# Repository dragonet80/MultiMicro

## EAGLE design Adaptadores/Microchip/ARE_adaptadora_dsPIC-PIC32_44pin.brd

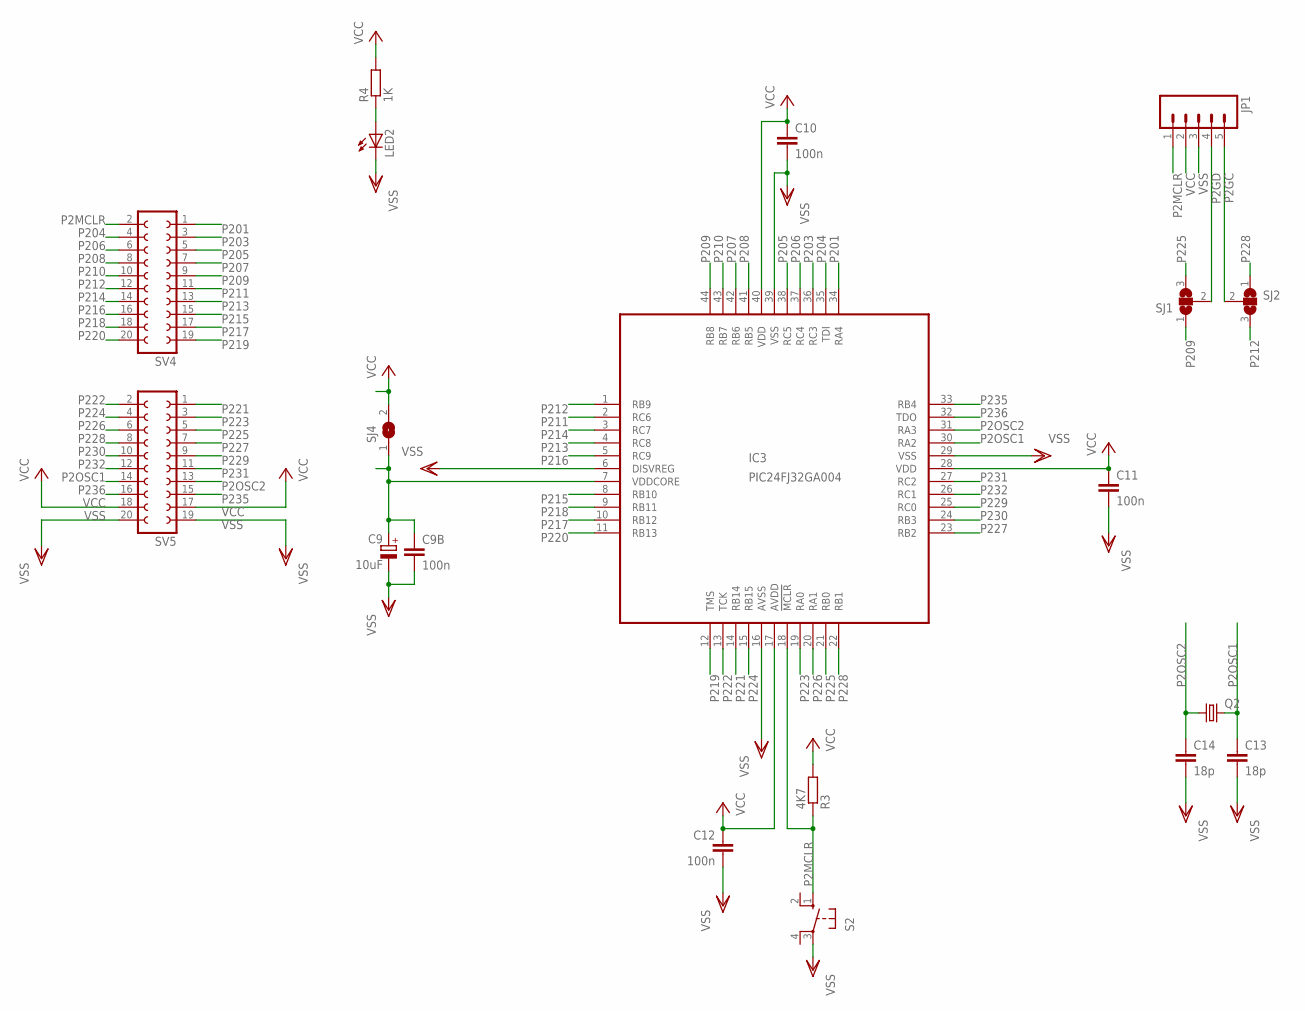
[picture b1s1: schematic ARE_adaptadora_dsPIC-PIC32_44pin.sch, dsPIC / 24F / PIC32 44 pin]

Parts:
C9: 10uF; SMC_C
C9B, C10, C11, C12: 100n; C0805
C13, C14: 18p; C0805
IC3: PIC24FJ32GA004; TQFP44
JP1: M05PTH; 1X05
LED2: LEDCHIPLED_0805; CHIPLED_0805
Q2: CRYSTALHC18U-V; HC18U-V
R3: 4K7; R0805
R4: 1K; R0805
S2: 10-XX; B3F-10XX; MPN B3F-1000
SJ1, SJ2: SJ2W; SJ_2
SJ4: SJ
SV4, SV5: FE10-2W

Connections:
unnamed: LED2.A, R4.1
unnamed: C9.+, C9B.1, IC3.7 (VDDCORE), SJ4.1
P2GC: JP1.5, SJ2.2
P2GD: JP1.4, SJ1.2
P2MCLR: IC3.18 (!MCLR), JP1.1, R3.1, S2.1 (S), SV4.2
P2OSC1: C13.1, IC3.30 (RA2), Q2.2, SV5.14
P2OSC2: C14.1, IC3.31 (RA3), Q2.1, SV5.13
P201: IC3.34 (RA4), SV4.1
P203: IC3.36 (RC3), SV4.3
P204: IC3.35 (TDI), SV4.4
P205: IC3.38 (RC5), SV4.5
P206: IC3.37 (RC4), SV4.6
P207: IC3.42 (RB6), SV4.7
P208: IC3.41 (RB5), SV4.8
P209: IC3.44 (RB8), SJ1.1, SV4.9
P210: IC3.43 (RB7), SV4.10
P211: IC3.2 (RC6), SV4.11
P212: IC3.1 (RB9), SJ2.3, SV4.12
P213: IC3.4 (RC8), SV4.13
P214: IC3.3 (RC7), SV4.14
P215: IC3.8 (RB10), SV4.15
P216: IC3.5 (RC9), SV4.16
P217: IC3.10 (RB12), SV4.17
P218: IC3.9 (RB11), SV4.18
P219: IC3.12 (TMS), SV4.19
P220: IC3.11 (RB13), SV4.20
P221: IC3.14 (RB14), SV5.1
P222: IC3.13 (TCK), SV5.2
P223: IC3.19 (RA0), SV5.3
P224: IC3.15 (RB15), SV5.4
P225: IC3.21 (RB0), SJ1.3, SV5.5
P226: IC3.20 (RA1), SV5.6
P227: IC3.23 (RB2), SV5.7
P228: IC3.22 (RB1), SJ2.1, SV5.8
P229: IC3.25 (RC0), SV5.9
P230: IC3.24 (RB3), SV5.10
P231: IC3.27 (RC2), SV5.11
P232: IC3.26 (RC1), SV5.12
P235: IC3.33 (RB4), SV5.15
P236: IC3.32 (TDO), SV5.16
VCC: C10.1, C11.1, C12.1, IC3.17 (AVDD), IC3.28 (VDD), IC3.40 (VDD), JP1.2, R3.2, R4.2, SJ4.2, SV5.17, SV5.18
VSS: C9.-, C9B.2, C10.2, C11.2, C12.2, C13.2, C14.2, IC3.6 (DISVREG), IC3.16 (AVSS), IC3.29 (VSS), IC3.39 (VSS), JP1.3, LED2.C, S2.3, SV5.19, SV5.20

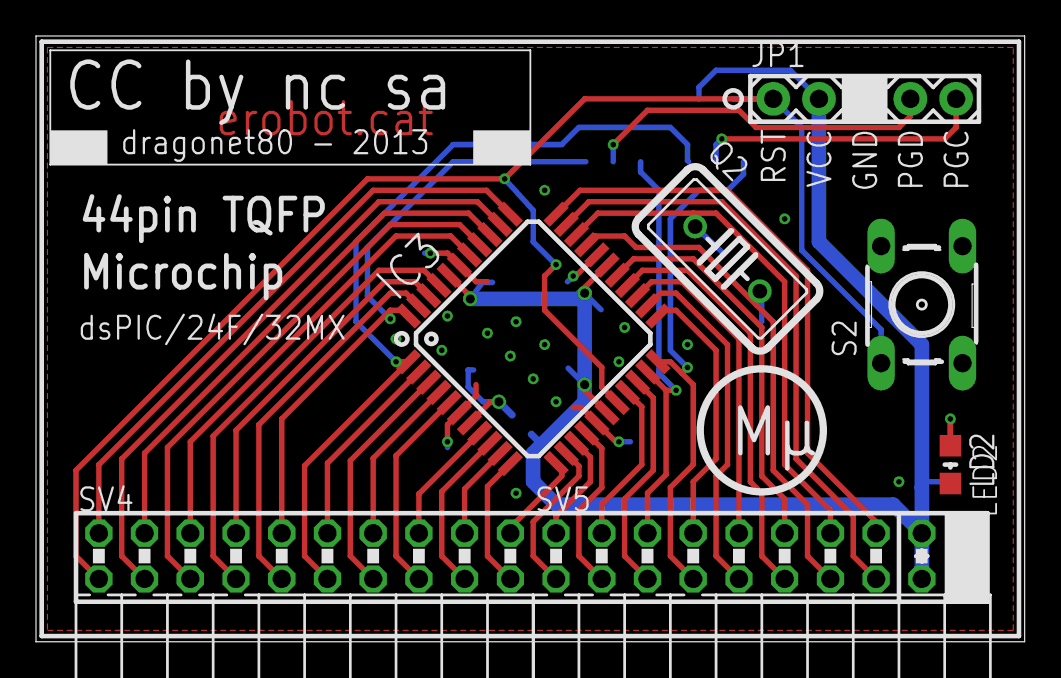
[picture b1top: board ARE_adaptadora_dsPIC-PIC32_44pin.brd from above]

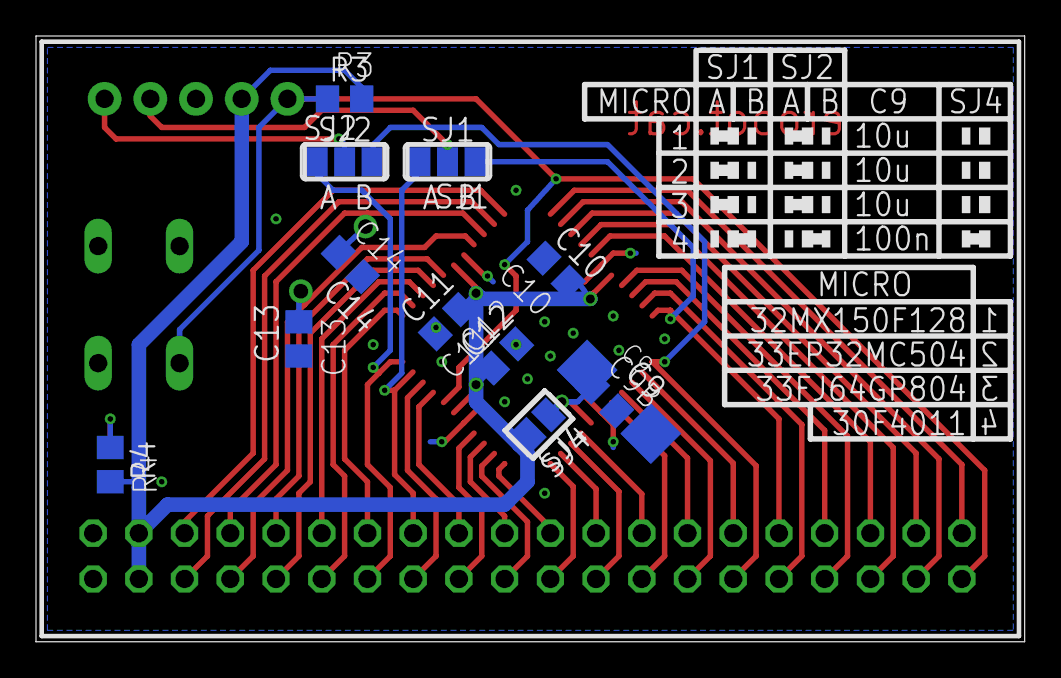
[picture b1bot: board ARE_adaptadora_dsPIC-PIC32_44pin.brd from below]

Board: 2 copper layers, 54.9 x 33.7 mm, 19 parts (12 on the bottom side), 42 nets.

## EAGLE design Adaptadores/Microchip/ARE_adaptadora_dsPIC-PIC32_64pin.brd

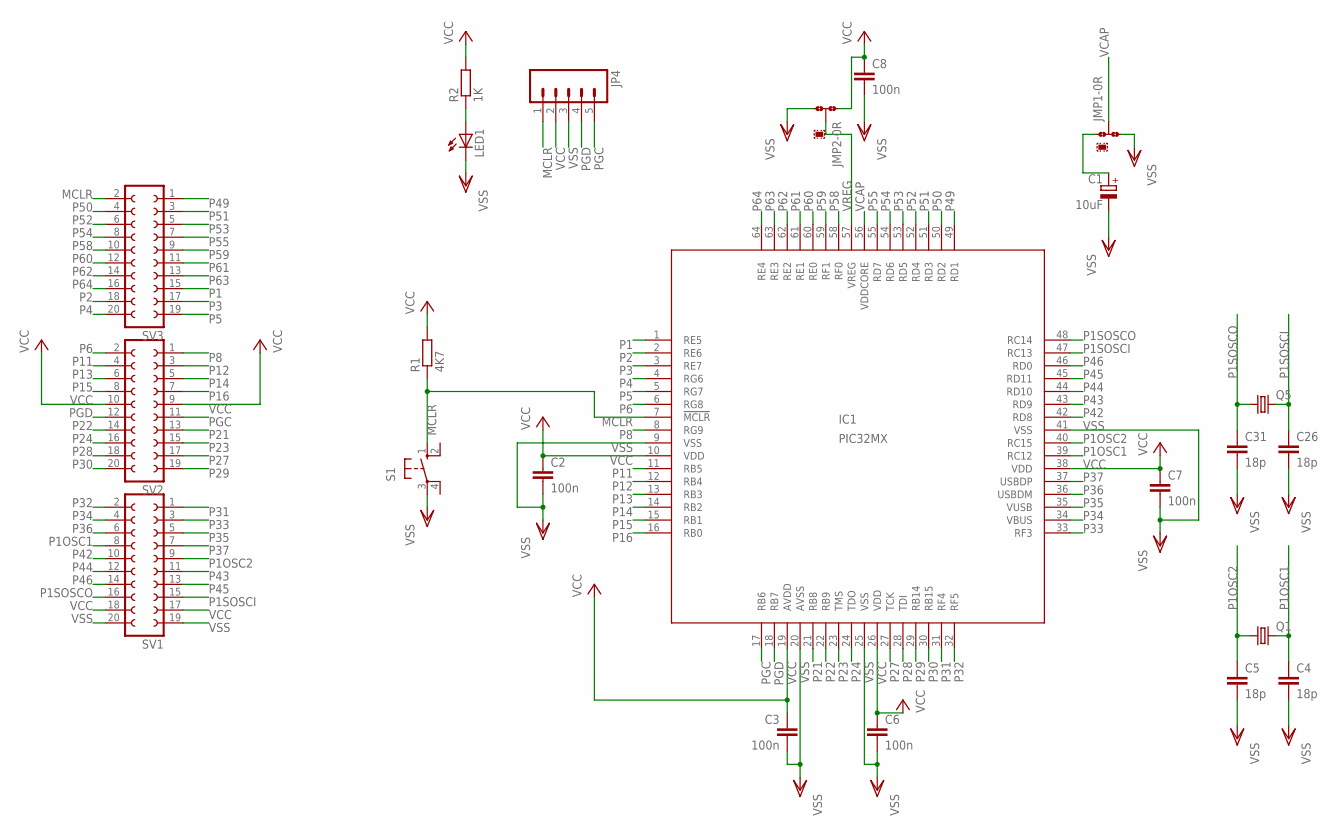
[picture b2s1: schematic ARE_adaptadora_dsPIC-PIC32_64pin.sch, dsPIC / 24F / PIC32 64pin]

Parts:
C1: 10uF; SMC_C
C2, C3, C6, C7, C8: 100n; C0805
C4, C5, C26, C31: 18p; C0805
IC1: PIC32MX; TQFP64-10X10
JMP1, JMP2: 0R-JUMPA; A0R-JMP
JP4: M05PTH; 1X05
LED1: LEDCHIPLED_0805; CHIPLED_0805
Q1, Q5: CRYSTALHC18U-V; HC18U-V
R1: 4K7; R0805
R2: 1K; R0805
S1: 10-XX; B3F-10XX; MPN B3F-1000
SV1, SV2, SV3: FE10-2W

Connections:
MCLR: IC1.7 (!MCLR), JP4.1, R1.1, S1.1 (S), SV3.2
unnamed: LED1.A, R2.1
unnamed: C1.+, JMP1.1
P1: IC1.1 (RE5), SV3.15
P1OSC1: C4.1, IC1.39 (RC12), Q1.2, SV1.8
P1OSC2: C5.1, IC1.40 (RC15), Q1.1, SV1.9
P1SOSCI: C26.1, IC1.47 (RC13), Q5.2, SV1.15
P1SOSCO: C31.1, IC1.48 (RC14), Q5.1, SV1.16
P2: IC1.2 (RE6), SV3.18
P3: IC1.3 (RE7), SV3.17
P4: IC1.4 (RG6), SV3.20
P5: IC1.5 (RG7), SV3.19
P6: IC1.6 (RG8), SV2.2
P8: IC1.8 (RG9), SV2.1
P11: IC1.11 (RB5), SV2.4
P12: IC1.12 (RB4), SV2.3
P13: IC1.13 (RB3), SV2.6
P14: IC1.14 (RB2), SV2.5
P15: IC1.15 (RB1), SV2.8
P16: IC1.16 (RB0), SV2.7
P21: IC1.21 (RB8), SV2.13
P22: IC1.22 (RB9), SV2.14
P23: IC1.23 (TMS), SV2.15
P24: IC1.24 (TDO), SV2.16
P27: IC1.27 (TCK), SV2.17
P28: IC1.28 (TDI), SV2.18
P29: IC1.29 (RB14), SV2.19
P30: IC1.30 (RB15), SV2.20
P31: IC1.31 (RF4), SV1.1
P32: IC1.32 (RF5), SV1.2
P33: IC1.33 (RF3), SV1.3
P34: IC1.34 (VBUS), SV1.4
P35: IC1.35 (VUSB), SV1.5
P36: IC1.36 (USBDM), SV1.6
P37: IC1.37 (USBDP), SV1.7
P42: IC1.42 (RD8), SV1.10
P43: IC1.43 (RD9), SV1.11
P44: IC1.44 (RD10), SV1.12
P45: IC1.45 (RD11), SV1.13
P46: IC1.46 (RD0), SV1.14
P49: IC1.49 (RD1), SV3.1
P50: IC1.50 (RD2), SV3.4
P51: IC1.51 (RD3), SV3.3
P52: IC1.52 (RD4), SV3.6
P53: IC1.53 (RD5), SV3.5
P54: IC1.54 (RD6), SV3.8
P55: IC1.55 (RD7), SV3.7
P58: IC1.58 (RF0), SV3.10
P59: IC1.59 (RF1), SV3.9
P60: IC1.60 (RE0), SV3.12
P61: IC1.61 (RE1), SV3.11
P62: IC1.62 (RE2), SV3.14
P63: IC1.63 (RE3), SV3.13
P64: IC1.64 (RE4), SV3.16
PGC: IC1.17 (RB6), JP4.5, SV2.11
PGD: IC1.18 (RB7), JP4.4, SV2.12
VCAP: IC1.56 (VDDCORE), JMP1.2
VCC: C2.1, C3.1, C6.1, C7.1, C8.1, IC1.10 (VDD), IC1.19 (AVDD), IC1.26 (VDD), IC1.38 (VDD), JMP2.1, JP4.2, R1.2, R2.2, SV1.17, SV1.18, SV2.9, SV2.10
VREG: IC1.57 (VREG), JMP2.2
VSS: C1.-, C2.2, C3.2, C4.2, C5.2, C6.2, C7.2, C8.2, C26.2, C31.2, IC1.9 (VSS), IC1.20 (AVSS), IC1.25 (VSS), IC1.41 (VSS), JMP1.3, JMP2.3, JP4.3, LED1.C, S1.3, SV1.19, SV1.20

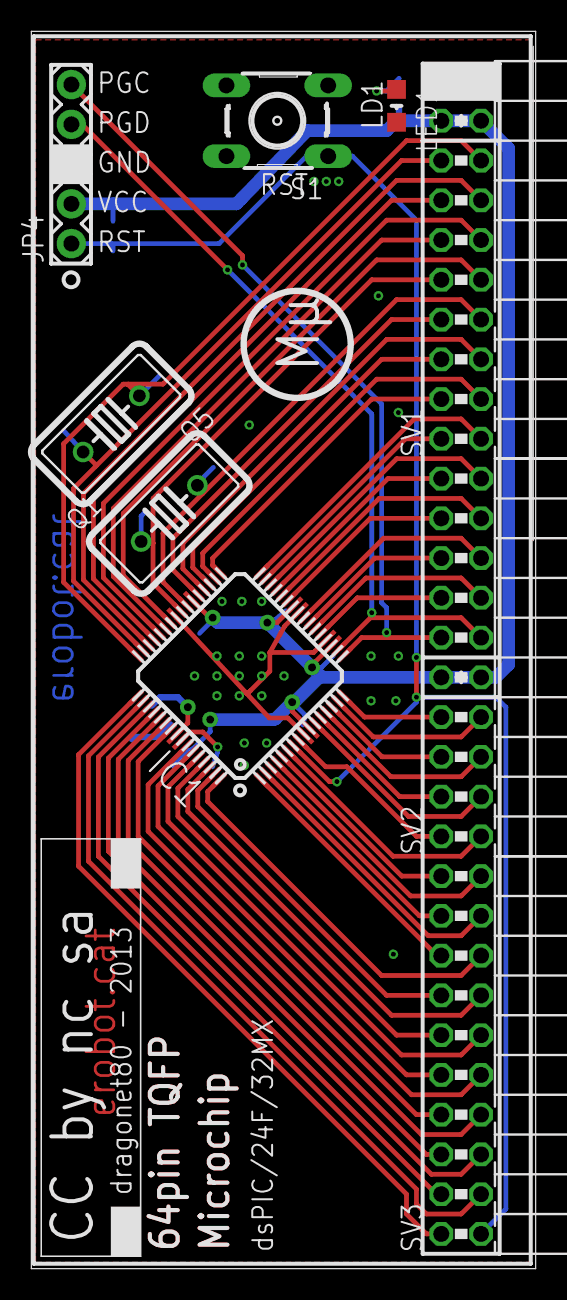
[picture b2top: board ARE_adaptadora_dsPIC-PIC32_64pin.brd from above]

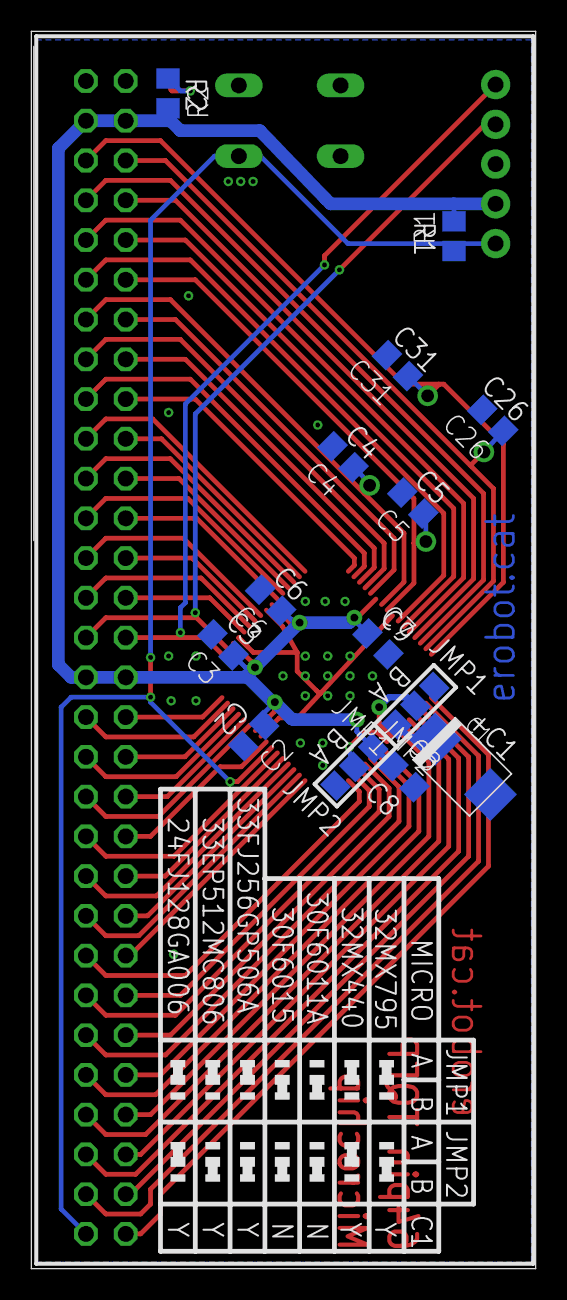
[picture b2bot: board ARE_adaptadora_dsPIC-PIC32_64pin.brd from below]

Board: 2 copper layers, 32.2 x 79.1 mm, 23 parts (14 on the bottom side), 60 nets.

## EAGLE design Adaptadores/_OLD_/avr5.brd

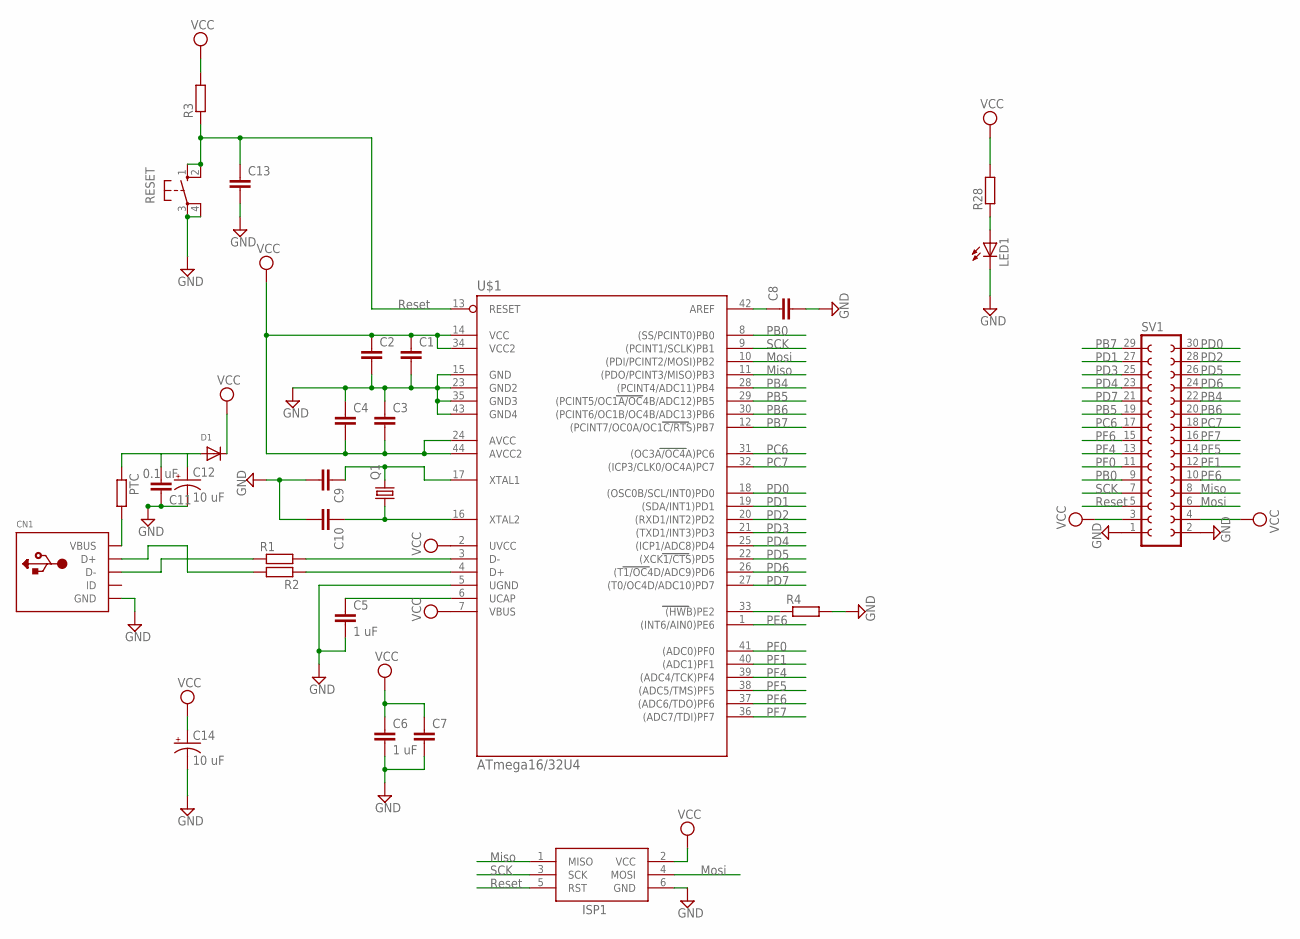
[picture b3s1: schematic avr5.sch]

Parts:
C1, C2, C3, C4, C7, C8, C9, C10, C13: C-EUC1206; C1206
C5, C6: 1 uF; C1206
C11: 0.1 uF; C1206
C12, C14: 10 uF; EIA3216
CN1: USBMINIB; USB-MINIB
D1: DIODESOD-123; SOD-123
ISP1: AVRISP-6; AVRISP
LED1: LEDCHIPLED_1206; CHIPLED_1206
PTC: R-EU_R1206; R1206
Q1: CRYSTALHC49UP; HC49UP
R1, R2, R3, R4, R28: R-EU_R1206; R1206
RESET: 10-XX; B3F-10XX
SV1: FE15-2
U$1: ATmega16/32U4; TQFP44

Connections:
GND: C1.2, C2.2, C3.1, C4.1, C5.2, C6.2, C7.2, C8.2, C9.2, C10.2, C11.2, C12.C (-), C13.2, C14.C (-), CN1.GND, ISP1.6 (GND), LED1.C, R4.2, RESET.3, RESET.4 (P1), SV1.1, SV1.2, U$1.5 (UGND), U$1.15 (GND), U$1.23 (GND2), U$1.35 (GND3), U$1.43 (GND4)
MISO: ISP1.1 (MISO), SV1.8, U$1.11 ((PDO/PCINT3/MISO)PB3)
MOSI: ISP1.4 (MOSI), SV1.6, U$1.10 ((PDI/PCINT2/MOSI)PB2)
unnamed: C9.1, Q1.2, U$1.17 (XTAL1)
unnamed: C10.1, Q1.1, U$1.16 (XTAL2)
unnamed: C5.1, U$1.6 (UCAP)
unnamed: R4.1, U$1.33 ((HWB)PE2)
unnamed: R2.1, U$1.4 (D+)
unnamed: R1.2, U$1.3 (D-)
unnamed: CN1.D+, R2.2
unnamed: CN1.D-, R1.1
unnamed: CN1.VBUS, PTC.2
unnamed: C11.1, C12.A (+), D1.A, PTC.1
unnamed: C8.1, U$1.42 (AREF)
unnamed: LED1.A, R28.1
PB0: SV1.9, U$1.8 ((SS/PCINT0)PB0)
PB4: SV1.22, U$1.28 ((PCINT4/ADC11)PB4)
PB5: SV1.19, U$1.29 ((PCINT5/OC1A/OC4B/ADC12)PB5)
PB6: SV1.20, U$1.30 ((PCINT6/OC1B/OC4B/ADC13)PB6)
PB7: SV1.29, U$1.12 ((PCINT7/OC0A/OC1C/RTS)PB7)
PC6: SV1.17, U$1.31 ((OC3A/OC4A)PC6)
PC7: SV1.18, U$1.32 ((ICP3/CLK0/OC4A)PC7)
PD0: SV1.30, U$1.18 ((OSC0B/SCL/INT0)PD0)
PD1: SV1.27, U$1.19 ((SDA/INT1)PD1)
PD2: SV1.28, U$1.20 ((RXD1/INT2)PD2)
PD3: SV1.25, U$1.21 ((TXD1/INT3)PD3)
PD4: SV1.23, U$1.25 ((ICP1/ADC8)PD4)
PD5: SV1.26, U$1.22 ((XCK1/CTS)PD5)
PD6: SV1.24, U$1.26 ((T1/OC4D/ADC9)PD6)
PD7: SV1.21, U$1.27 ((T0/OC4D/ADC10)PD7)
PE6: SV1.10, U$1.1 ((INT6/AIN0)PE6)
PF0: SV1.11, U$1.41 ((ADC0)PF0)
PF1: SV1.12, U$1.40 ((ADC1)PF1)
PF4: SV1.13, U$1.39 ((ADC4/TCK)PF4)
PF5: SV1.14, U$1.38 ((ADC5/TMS)PF5)
PF6: SV1.15, U$1.37 ((ADC6/TDO)PF6)
PF7: SV1.16, U$1.36 ((ADC7/TDI)PF7)
RESET: C13.1, ISP1.5 (RST), R3.1, RESET.1 (S), RESET.2 (S1), SV1.5, U$1.13 (RESET)
SCK: ISP1.3 (SCK), SV1.7, U$1.9 ((PCINT1/SCLK)PB1)
VCC: C1.1, C2.1, C3.2, C4.2, C6.1, C7.1, C14.A (+), D1.C, ISP1.2 (VCC), R3.2, R28.2, SV1.3, SV1.4, U$1.2 (UVCC), U$1.7 (VBUS), U$1.14 (VCC), U$1.24 (AVCC), U$1.34 (VCC2), U$1.44 (AVCC2)

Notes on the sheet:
Reset
Miso
Mosi
SCK
PB7
PB6
PB5
PB4
PB0
PC6
PC7
PD0
PD1
PD2
PD3
PD4
PD5
PD6
PD7
PE6
PF0
PF1
PF4
PF5
PF6
PF7

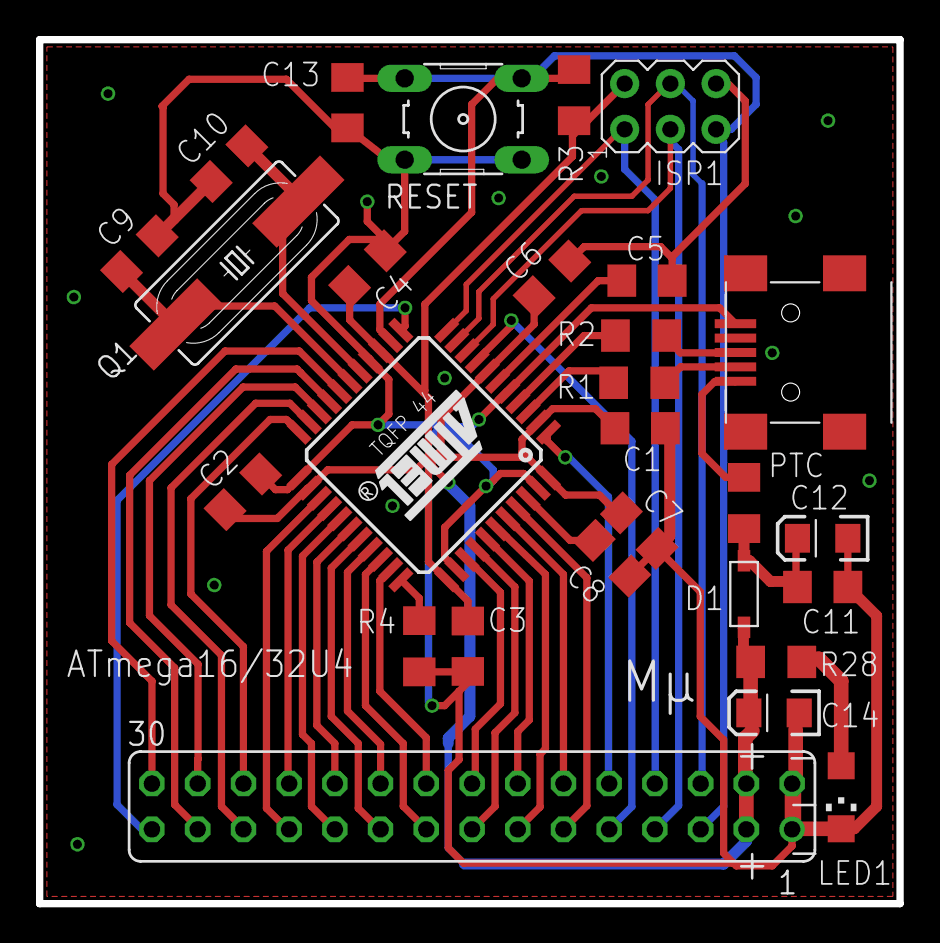
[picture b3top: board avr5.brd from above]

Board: 2 copper layers, 47.8 x 48.0 mm, 28 parts (0 on the bottom side), 40 nets.

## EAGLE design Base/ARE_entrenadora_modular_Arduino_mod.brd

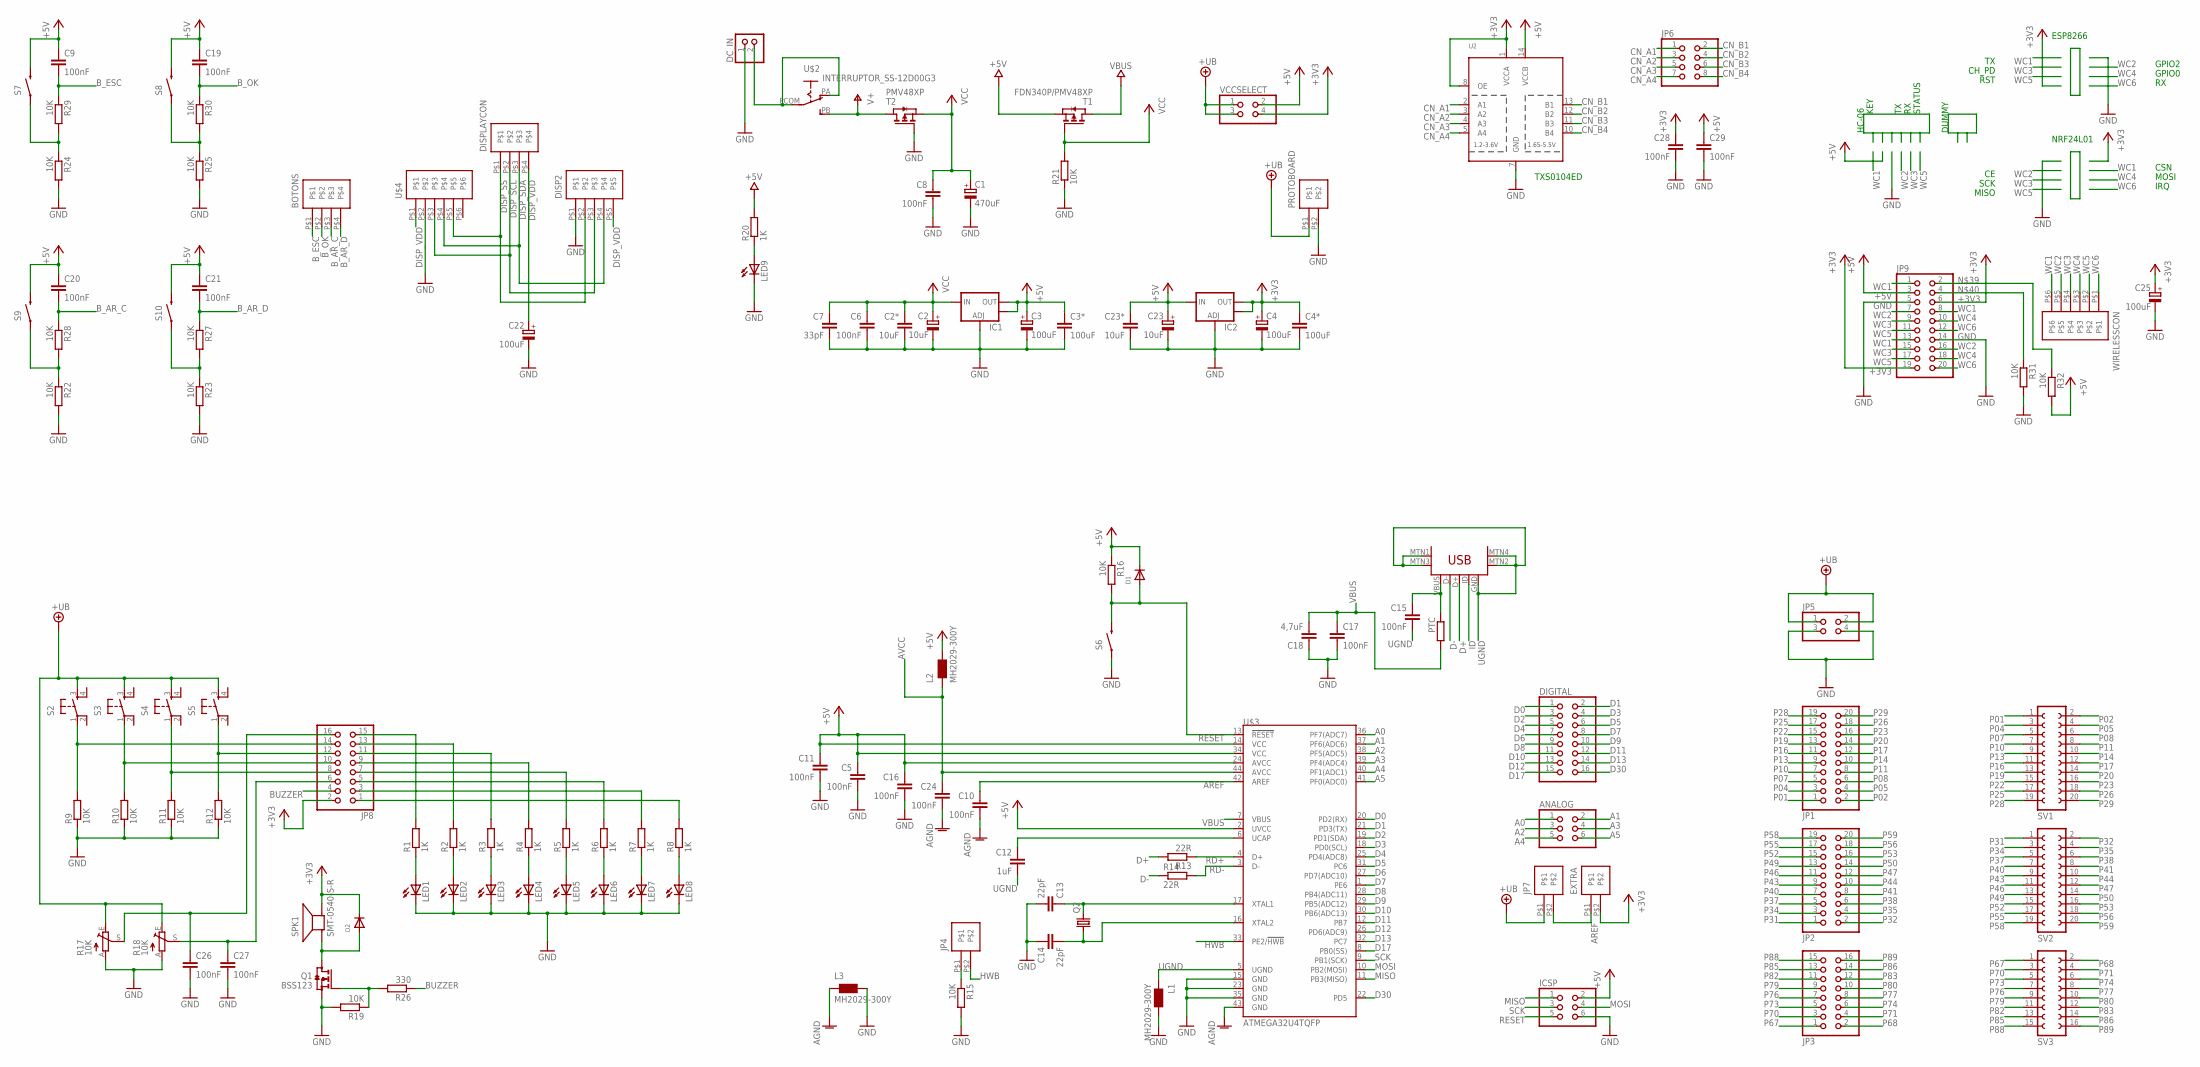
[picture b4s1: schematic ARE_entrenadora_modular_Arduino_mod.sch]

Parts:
ANALOG: PINHD-2X3; 2X03
BOTONS: PINHEAD_1X4; PINHEAD_1X4_2.54
C1: 470uF; E3,5-8
C2, C23: 10uF; SMC_C
C2*, C23*: 10uF; C1206
C3, C4: 100uF; CT7343
C3*, C4*: 100uF; C1206
C5, C6, C8, C9, C10, C11, C15, C16, C17, C19, C20, C21, C24, C26, C27, C28, C29: 100nF; C0805
C7: 33pF; C0805
C12: 1uF; C0805
C13, C14: 22pF; C0805
C18: 4,7uF; C0805
C22, C25: 100uF; SMC_C
D1, D2: DIODESOD-123; SOD-123
DC_IN: PINHD-1X2/90; 1X02/90
DIGITAL: PINHD-2X8; 2X08
DISP2: PINHEAD_1X5; PINHEAD_1X5_2.54
DISPLAYCON: PINHEAD_1X4; PINHEAD_1X4_2.54
EXTRA: PINHEAD_1X2; PINHEAD_1X2_2.54
IC1, IC2: V_REG_LM1117SOT223; SOT223
ICSP: PINHD-2X3; 2X03
JP1, JP2: PINHD-2X10/90; 2X10/90
JP3: PINHD-2X8/90; 2X08/90
JP4, JP7: PINHEAD_1X2; PINHEAD_1X2_2.54
JP5: PINHD-2X2/90; 2X02/90
JP6: PINHD-2X4; 2X04
JP8: PINHD-2X8; 2X08
JP9: PINHD-2X10; 2X10
L1, L2, L3: MH2029-300Y; 0805
LED1, LED2, LED3, LED4, LED5, LED6, LED7, LED8, LED9: LEDCHIP-LED0805; CHIP-LED0805
PROTOBOARD: PINHEAD_1X2; PINHEAD_1X2_2.54
PTC: R-EU_R1206; R1206
Q1: BSS123; SOT23
Q2: CRYSTALHC49UP; HC49UP
R1, R2, R3, R4, R5, R6, R7, R8, R20: 1K; R0805
R9, R10, R11, R12, R15, R16, R19, R21, R22, R23, R24, R25, R27, R28, R29, R30, R31, R32: 10K; R0805
R13, R14: 22R; R0805
R17, R18: 10K; CA6V
R26: 330; R0805
S2, S3, S4, S5: TAC_SWITCHPTH; TACTILE-PTH
S6, S7, S8, S9, S10: SWITCH-MOMENTARY-2-SMD-1101NE; TACTILE-SWITCH-1101NE
SPK1: SMT-0540-S-R
SV1, SV2: FE10-2
SV3: FE08-2
T1: FDN340P/PMV48XP; SOT-23
T2: PMV48XP; SOT-23
U2: TXB0104PWRSOIC14; SO14
U$1: USB-MINIB-5PIN; USB-MINIB
U$2: INTERRUPTOR_SS-12D00G3; SS-12D00G3
U$3: ATMEGA32U4TQFP; SPARKFUN-DIGITALIC_TQFP44
U$4: PINHEAD_1X6; PINHEAD_1X6_2.54
VCCSELECT: PINHD-2X2; 2X02
WIRELESSCON: PINHEAD_1X6; PINHEAD_1X6_2.54

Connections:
+3V3: C4.+, C4*.1, C25.+, C28.1, D2.C, EXTRA.P$2, IC2.2 (OUT), IC2.4 (OUT), JP8.2, JP9.6, JP9.19, SPK1.+ (-), U2.1 (VCCA), U2.8 (OE), VCCSELECT.4
+5V: C3.+, C3*.1, C5.1, C9.1, C11.1, C16.1, C19.1, C20.1, C21.1, C23.+, C23*.1, C29.1, D1.C, IC1.2 (OUT), IC1.4 (OUT), IC2.3 (IN), ICSP.2, JP9.3, L2.2, R16.1, R20.2, R32.2, S7.P$2 (2), S8.P$2 (2), S9.P$2 (2), S10.P$2 (2), T1.2 (S), U2.14 (VCCB), U$3.2 (UVCC), U$3.14 (VCC), U$3.24 (AVCC), U$3.34 (VCC), VCCSELECT.2
+UB: JP5.1, JP5.2, JP7.P$1, PROTOBOARD.P$1, R17.E, R18.E, S2.3, S3.3, S4.3, S5.3, VCCSELECT.1, VCCSELECT.3
A0: ANALOG.1, U$3.36 (PF7(ADC7))
A1: ANALOG.2, U$3.37 (PF6(ADC6))
A2: ANALOG.3, U$3.38 (PF5(ADC5))
A3: ANALOG.4, U$3.39 (PF4(ADC4))
A4: ANALOG.5, U$3.40 (PF1(ADC1))
A5: ANALOG.6, U$3.41 (PF0(ADC0))
AGND: C10.2, C24.2, L3.1, U$3.43 (GND)
AREF: C10.1, EXTRA.P$1, JP7.P$2, U$3.42 (AREF)
AVCC: C24.1, L2.1, U$3.44 (AVCC)
BUZZER: JP8.4, R26.1
B_AR_C: BOTONS.P$3, C20.2, R28.1
B_AR_D: BOTONS.P$4, C21.2, R27.1
B_ESC: BOTONS.P$1, C9.2, R29.1
B_OK: BOTONS.P$2, C19.2, R30.1
CN_A1: JP6.1, U2.2 (A1)
CN_A2: JP6.3, U2.3 (A2)
CN_A3: JP6.5, U2.4 (A3)
CN_A4: JP6.7, U2.5 (A4)
CN_B1: JP6.2, U2.13 (B1)
CN_B2: JP6.4, U2.12 (B2)
CN_B3: JP6.6, U2.11 (B3)
CN_B4: JP6.8, U2.10 (B4)
D0: DIGITAL.1, U$3.20 (PD2(RX))
D1: DIGITAL.2, U$3.21 (PD3(TX))
D2: DIGITAL.3, U$3.19 (PD1(SDA))
D3: DIGITAL.4, U$3.18 (PD0(SCL))
D4: DIGITAL.5, U$3.25 (PD4(ADC8))
D5: DIGITAL.6, U$3.31 (PC6)
D6: DIGITAL.7, U$3.27 (PD7(ADC10))
D7: DIGITAL.8, U$3.1 (PE6)
D8: DIGITAL.9, U$3.28 (PB4(ADC11))
D9: DIGITAL.10, U$3.29 (PB5(ADC12))
D10: DIGITAL.11, U$3.30 (PB6(ADC13))
D11: DIGITAL.12, U$3.12 (PB7)
D12: DIGITAL.13, U$3.26 (PD6(ADC9))
D13: DIGITAL.14, U$3.32 (PC7)
D17: DIGITAL.15, U$3.8 (PB0(SS))
D30: DIGITAL.16, U$3.22 (PD5)
D+: R13.2, U$1.D+
D-: R14.1, U$1.D-
DISP_SCL: DISP2.P$3, DISPLAYCON.P$2, U$4.P$3
DISP_SDA: DISP2.P$4, DISPLAYCON.P$3, U$4.P$4
DISP_SS: DISP2.P$2, DISPLAYCON.P$1, U$4.P$5
DISP_VDD: C22.+, DISP2.P$5, DISPLAYCON.P$4, U$4.P$1
GND: C1.-, C2.-, C2*.2, C3.-, C3*.2, C4.-, C4*.2, C5.2, C6.2, C7.2, C8.2, C11.2, C13.2, C14.1, C16.2, C17.2, C18.1, C22.-, C23.-, C23*.2, C25.-, C26.2, C27.2, C28.2, C29.2, DC_IN.1, DISP2.P$1, IC1.1 (ADJ), IC2.1 (ADJ), ICSP.6, JP5.3, JP5.4, JP9.5, JP9.14, L1.2, L3.2, LED1.C, LED2.C, LED3.C, LED4.C, LED5.C, LED6.C, LED7.C, LED8.C, LED9.C, PROTOBOARD.P$2, Q1.2 (S), R9.1, R10.1, R11.1, R12.1, R15.2, R17.A, R18.A, R19.2, R21.1, R22.2, R23.2, R24.2, R25.2, R31.2, S6.P$1 (1), T2.3 (G), U2.7 (GND), U$3.15 (GND), U$3.23 (GND), U$3.35 (GND), U$4.P$2
HWB: JP4.P$2, U$3.33 (PE2/!HWB)
ID: U$1.ID
MISO: ICSP.1, U$3.11 (PB3(MISO))
MOSFET_BASE: Q1.1 (G), R19.1, R26.2
MOSI: ICSP.4, U$3.10 (PB2(MOSI))
unnamed: LED1.A, R1.1
unnamed: LED2.A, R2.1
unnamed: LED3.A, R3.1
unnamed: LED4.A, R4.1
unnamed: JP8.13, R2.2
unnamed: JP8.11, R3.2
unnamed: JP8.15, R1.2
unnamed: JP8.9, R4.2
unnamed: LED9.A, R20.1
unnamed: C27.1, JP8.6, R18.S
unnamed: D2.A, Q1.3 (D), SPK1.- (+)
unnamed: JP4.P$1, R15.1
unnamed: C13.1, Q2.2, U$3.17 (XTAL1)
unnamed: C14.2, Q2.1, U$3.16 (XTAL2)
unnamed: R22.1, R28.2, S9.P$1 (1)
unnamed: JP8.8, R11.2, S4.1
unnamed: JP8.12, R12.2, S5.1
unnamed: C15.1, PTC.1, U$1.VBUS
unnamed: R24.1, R29.2, S7.P$1 (1)
unnamed: LED5.A, R5.1
unnamed: R25.1, R30.2, S8.P$1 (1)
unnamed: JP8.10, R10.2, S3.1
unnamed: R23.1, R27.2, S10.P$1 (1)
unnamed: C12.1, U$3.6 (UCAP)
unnamed: JP9.2, R32.1
unnamed: JP9.4, R31.1
unnamed: DC_IN.2, U$2.PA, U$2.PCOM
unnamed: LED6.A, R6.1
unnamed: LED7.A, R7.1
unnamed: LED8.A, R8.1
unnamed: JP8.14, R9.2, S2.1
unnamed: C26.1, JP8.16, R17.S
unnamed: JP8.5, R6.2
unnamed: JP8.3, R7.2
unnamed: JP8.7, R5.2
unnamed: JP8.1, R8.2
P01: JP1.1, SV1.1
P02: JP1.2, SV1.2
P04: JP1.3, SV1.3
P05: JP1.4, SV1.4
P07: JP1.5, SV1.5
P08: JP1.6, SV1.6
P10: JP1.7, SV1.7
P11: JP1.8, SV1.8
P13: JP1.9, SV1.9
P14: JP1.10, SV1.10
P16: JP1.11, SV1.11
P17: JP1.12, SV1.12
P19: JP1.13, SV1.13
P20: JP1.14, SV1.14
P22: JP1.15, SV1.15
P23: JP1.16, SV1.16
P25: JP1.17, SV1.17
P26: JP1.18, SV1.18
P28: JP1.19, SV1.19
P29: JP1.20, SV1.20
P31: JP2.1, SV2.1
P32: JP2.2, SV2.2
P34: JP2.3, SV2.3
P35: JP2.4, SV2.4
P37: JP2.5, SV2.5
P38: JP2.6, SV2.6
P40: JP2.7, SV2.7
P41: JP2.8, SV2.8
P43: JP2.9, SV2.9
P44: JP2.10, SV2.10
P46: JP2.11, SV2.11
P47: JP2.12, SV2.12
P49: JP2.13, SV2.13
P50: JP2.14, SV2.14
P52: JP2.15, SV2.15
P53: JP2.16, SV2.16
P55: JP2.17, SV2.17
P56: JP2.18, SV2.18
P58: JP2.19, SV2.19
P59: JP2.20, SV2.20
P67: JP3.1, SV3.1
P68: JP3.2, SV3.2
P70: JP3.3, SV3.3
P71: JP3.4, SV3.4
P73: JP3.5, SV3.5
P74: JP3.6, SV3.6
P76: JP3.7, SV3.7
P77: JP3.8, SV3.8
P79: JP3.9, SV3.9
P80: JP3.10, SV3.10
P82: JP3.11, SV3.11
P83: JP3.12, SV3.12
P85: JP3.13, SV3.13
P86: JP3.14, SV3.14
P88: JP3.15, SV3.15
P89: JP3.16, SV3.16
RD+: R13.1, U$3.4 (D+)
RD-: R14.2, U$3.3 (D-)
RESET: D1.A, ICSP.5, R16.2, S6.P$2 (2), U$3.13 (!RESET)
SCK: ICSP.3, U$3.9 (PB1(SCK))
UGND: C12.2, C15.2, L1.1, U$1.GND, U$1.MTN1 (MTN2), U$1.MTN2 (MTN3), U$1.MTN3 (MTN1), U$1.MTN4, U$3.5 (UGND)
V+: T2.1 (D), U$2.PB
VBUS: C17.1, C18.2, PTC.2, T1.1 (D), U$3.7 (VBUS)
VCC: C1.+, C2.+, C2*.1, C6.1, C7.1, C8.1, IC1.3 (IN), R21.2, T1.3 (G), T2.2 (S)
WC1: JP9.1, JP9.8, JP9.13, WIRELESSCON.P$6
WC2: JP9.7, JP9.16, WIRELESSCON.P$5
WC3: JP9.9, JP9.15, WIRELESSCON.P$4
WC4: JP9.10, JP9.18, WIRELESSCON.P$3
WC5: JP9.11, JP9.17, WIRELESSCON.P$2
WC6: JP9.12, JP9.20, WIRELESSCON.P$1

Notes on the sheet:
TXS0104ED
KEY
STATUS
CH_PD
RST
SCK
MISO
GPIO2
GPIO0
CSN
MOSI
IRQ
HC-06
DUMMY
NRF24L01
ESP8266

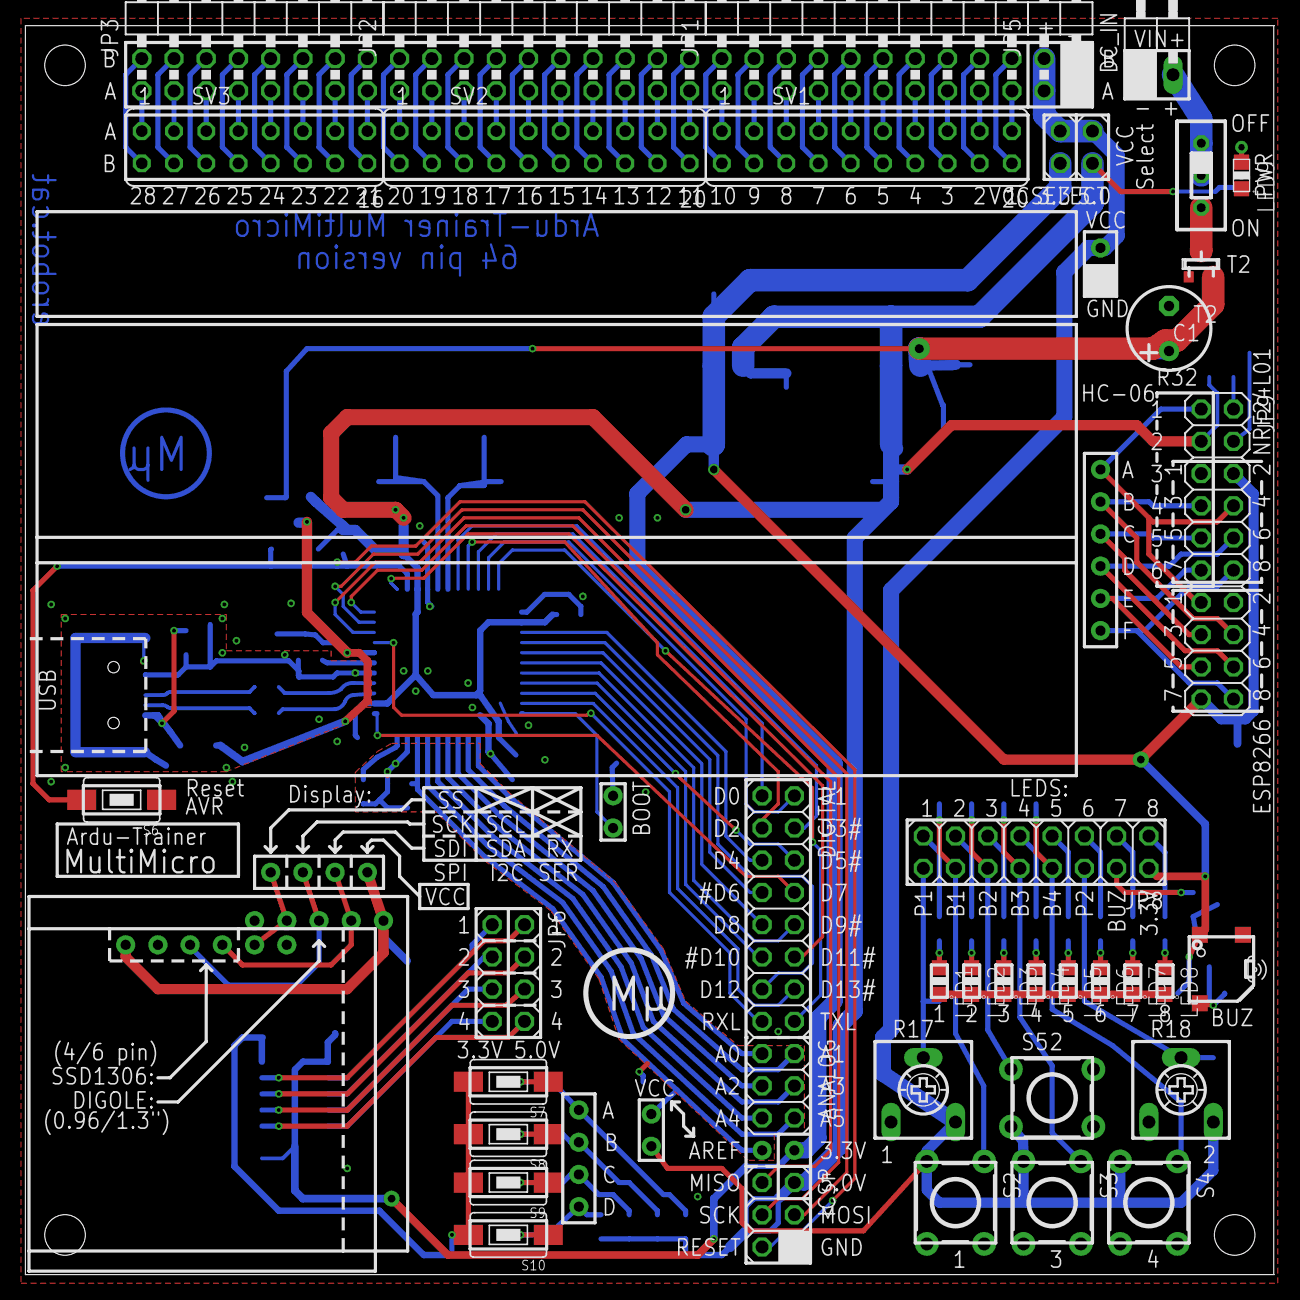
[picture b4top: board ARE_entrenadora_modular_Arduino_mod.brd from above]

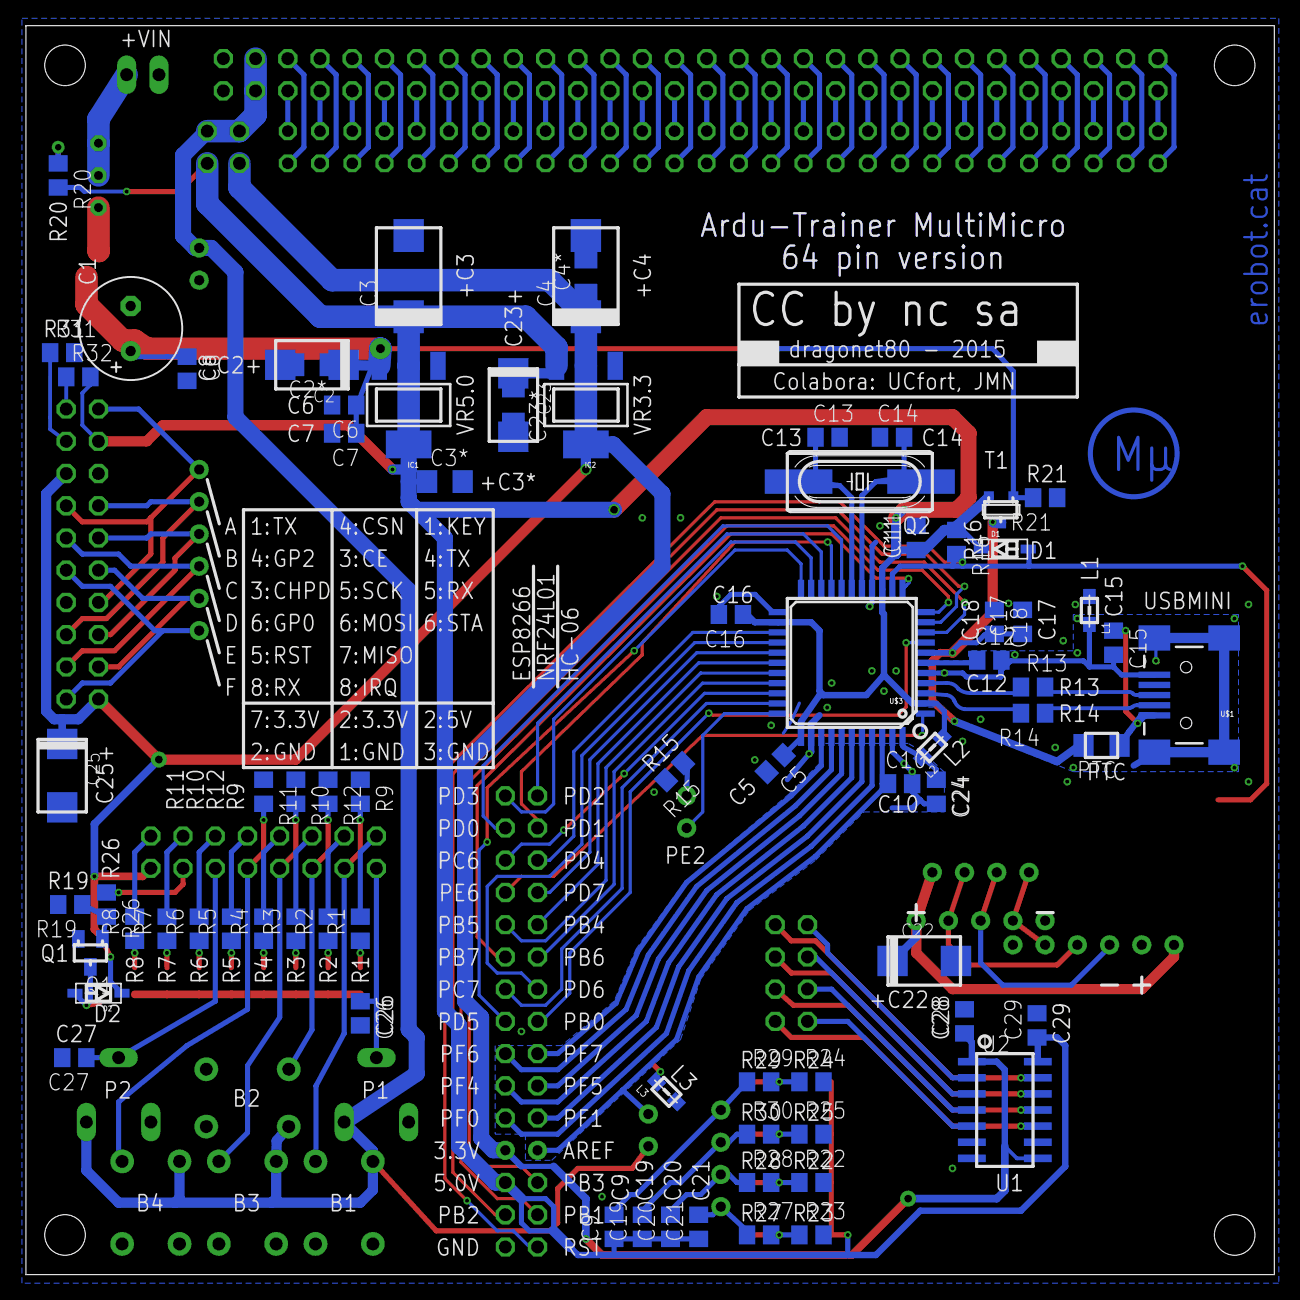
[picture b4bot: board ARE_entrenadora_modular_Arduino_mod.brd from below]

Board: 2 copper layers, 98.4 x 98.5 mm, 124 parts (77 on the bottom side), 158 nets.

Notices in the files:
Adaptadores/Microchip/ARE_adaptadora_dsPIC-PIC32_44pin.brd:
CC by nc sa
parts and their libraries:
SparkFun-Capacitors: Licensing: CC v3.0 Share-Alike You are welcome to use this library for commercial purposes.
SparkFun-Electromechanical: Licensing: Creative Commons ShareAlike 4.0 International - https://creativecommons.org/licenses/by-sa/4.0
